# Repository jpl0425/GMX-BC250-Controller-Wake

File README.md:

# GMX BC-250 Controller Wake (Rev 1.2)

Grumblymanx Mods — turns an AMD BC-250 (running Bazzite) **on** when you switch on an
**Xbox Series X|S controller**, using a Raspberry Pi **Pico W** or **Pico 2 W**.

The Pico stays powered from the ATX power supply's +5VSB standby line and listens for the
controller's Bluetooth LE broadcast. When it hears a saved controller it (optionally) switches
the power supply on via PS_ON, "presses" the BC-250 power button with a MOSFET, then waits for
the BC-250's "PC is on" signal (TPMS1 pin 9). The controller still connects to the BC-250 as normal.

> **Status:** firmware compiles cleanly for both boards but has **not yet been tested on real hardware**. The Pico shell has **not been test-printed yet**.

## Revisions
| Folder | What it is |
|---|---|
| `Rev 1.2/` | **Newest.** Install guide Rev 1.2: two completely separate install options (A: power supply always on, B: Pico switches the power supply), one step per page, a realistic picture for every step, page numbers for each option on the first page. Firmware Rev 1 (unchanged). Includes the 3D-printed Pico Shell. |
| `Rev 1.1/` | Previous: guide Rev 1.1 with BC-250 / ATX renders, firmware Rev 1, Pico Shell Rev 1. |

Inside `Rev 1.2/`:
| Folder | Contents |
|---|---|
| `Firmware/` | `GMX-BC250-Wake_Rev1_PicoW.uf2` (Pico W, RP2040) and `GMX-BC250-Wake_Rev1_Pico2W.uf2` (Pico 2 W, RP2350) |
| `Docs/` | Install guide (PDF) — start here, choose Option A or B on page 1. Also the Pico Shell print/assembly guide |
| `Renders/` | Every step picture (`S_A..` Option A, `S_B..` Option B, others shared) + BC-250 renders R1–R4 + Pico Shell pictures |
| `STL/`, `STEP/` | Pico Shell enclosure print and CAD files |
| `Source/` | Firmware source (Pico SDK 2.2.0 + BTstack), Pico Shell source, and the scripts that make the pictures and the guide |

## Optional PCB — GMX BC-250 Wake Board (+ 3D-printed shell)
A small board that replaces the perfboard build. The Pico W / Pico 2 W plugs into two 1x20 sockets;
BSS138LT1G MOSFETs (Q1, Q2), 1N5819WS diode (D1), resistors and the SW1 button are on the board;
outside wires solder to six labelled pads (J3–J8). Works for Option A and Option B (Option A: Q2, R2 and J5 not needed). Same firmware.

| Folder | What it is |
|---|---|
| `PCB/GMX-BC250-Wake-Board_Rev1.1/` | **Newest.** 70.5 × 43 mm board with 4 × M3 mounting holes, plus the 3D-printed **Wake Board Shell Rev 1** (Base, Button, 4 lids: GMX-Mods, Bazzite, BC-250, Blank) and its print/assembly guide |
| `PCB/GMX-BC250-Wake-Board_Rev1.0/` | Previous: 58 × 43 mm board, no mounting holes (does not fit the shell) |

Inside each PCB folder: `Gerbers/`, `BOM/`, `JLC_BOM/`, `CPL/`, `ibom/`, `Renders/`, `Docs/` (wiring diagrams, reports, shell guide), `Firmware/`, `Source/`; Rev 1.1 also has `STL/` and `STEP/` for the shell.

> The PCB and the shell have **not been ordered, printed or tested yet**.

## Pins (Pico GPIO)
GP2 power-button MOSFET · GP3 PS_ON MOSFET (Option B) · GP4 PC-on sense · GP5 optional button · GP6 optional LED · VSYS ← +5VSB through a Schottky diode

## Credits
Wake method from **dexikdex** (ESP32-BC250-LOP_PSU-PowerON-Xbox) and **GreatApo** (BC250_ESP32_ATX_PSU).
BC-250 details from **tfabris/BC-250** and the **elektricm amd-bc250-docs**. New Pico firmware written for this project.

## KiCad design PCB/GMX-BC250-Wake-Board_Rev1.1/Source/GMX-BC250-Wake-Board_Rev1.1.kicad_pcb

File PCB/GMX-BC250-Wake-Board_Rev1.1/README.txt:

GMX BC-250 Wake Board - Rev 1.1  (GMX Mods)
============================================

A small PCB that replaces the perfboard build of the GMX BC-250 Controller Wake
project. A Raspberry Pi Pico W or Pico 2 W plugs into two 1x20 sockets on the board.
Same firmware as the Controller Wake project (Firmware folder) - no changes.

Board: 70.5 x 43 mm, 2 layers, ground pour both sides, 4 x M3 mounting holes (H1-H4).
Rev 1.1 change: board widened and 4 M3 holes added for the 3D-printed shell. Circuit unchanged.
Outside wires solder to 6 labelled wire pads along the top edge (J3-J8).
Works for Option A (power supply always on) and Option B (Pico switches the supply).
For Option A, Q2 and R2 can be left off and J5 stays empty.

FOLDERS
  Gerbers   Gerber + drill zip - upload this to JLCPCB to order the bare board
  BOM       full parts list with LCSC numbers
  JLC_BOM   BOM in JLCPCB's format (SMD parts only) - only if JLCPCB fits the parts
  CPL       placement file for JLCPCB (SMD parts only) - only if JLCPCB fits the parts
  ibom      interactive BOM - open in a web browser while hand-soldering
  Renders   pictures of the board (bare, with parts, with the Pico) and of the shell
  STL       3D-printed shell, print-ready: Base, Button and 4 lids (print one lid)
  STEP      3D-printed shell CAD files
  Docs      wiring diagrams (Option A, Option B), shell print/assembly guide (PDF),
            DRC report, cross-check report, shell fit-check report
  Firmware  .uf2 files: PicoW for a Pico W, Pico2W for a Pico 2 W
  Source    KiCad 7 board, footprint libraries, build scripts; Source/shell = shell CadQuery source

PARTS
  Q1, Q2  BSS138LT1G      SOT-23   LCSC C82045
  R1, R2  10k 0603        YAGEO RC0603FR-0710KL   LCSC C98220
  R3      1k 0603         YAGEO RC0603FR-071KL    LCSC C22548
  D1      1N5819WS        SOD-323  LCSC C191023
  SW1     TS-1187A-B-A-B  5.1 x 5.1 mm SMD button  LCSC C318884
  J1, J2  female socket 1x20, 2.54 mm  ZHOURI PM2.54-1*20  LCSC C5224030
          (alternative: BOOMELE 2.54-1*20P, LCSC C50984)
  Q2 and R2: Option B only.

ORIENTATION
  D1: the band on the part goes toward the right edge of the board (silkscreen bar).
  Q1, Q2: the dot on the silkscreen marks the gate (pin 1).
  Pico: parts side up, USB end at the right edge ("Pin 1" is printed on the board).

SHELL
  Print Base + Button + one lid. 4 x M3 x 6 mm pan-head screws hold the board.
  Start with Docs/GMX-BC250-Wake-Board-Shell_Rev1_Guide.pdf.

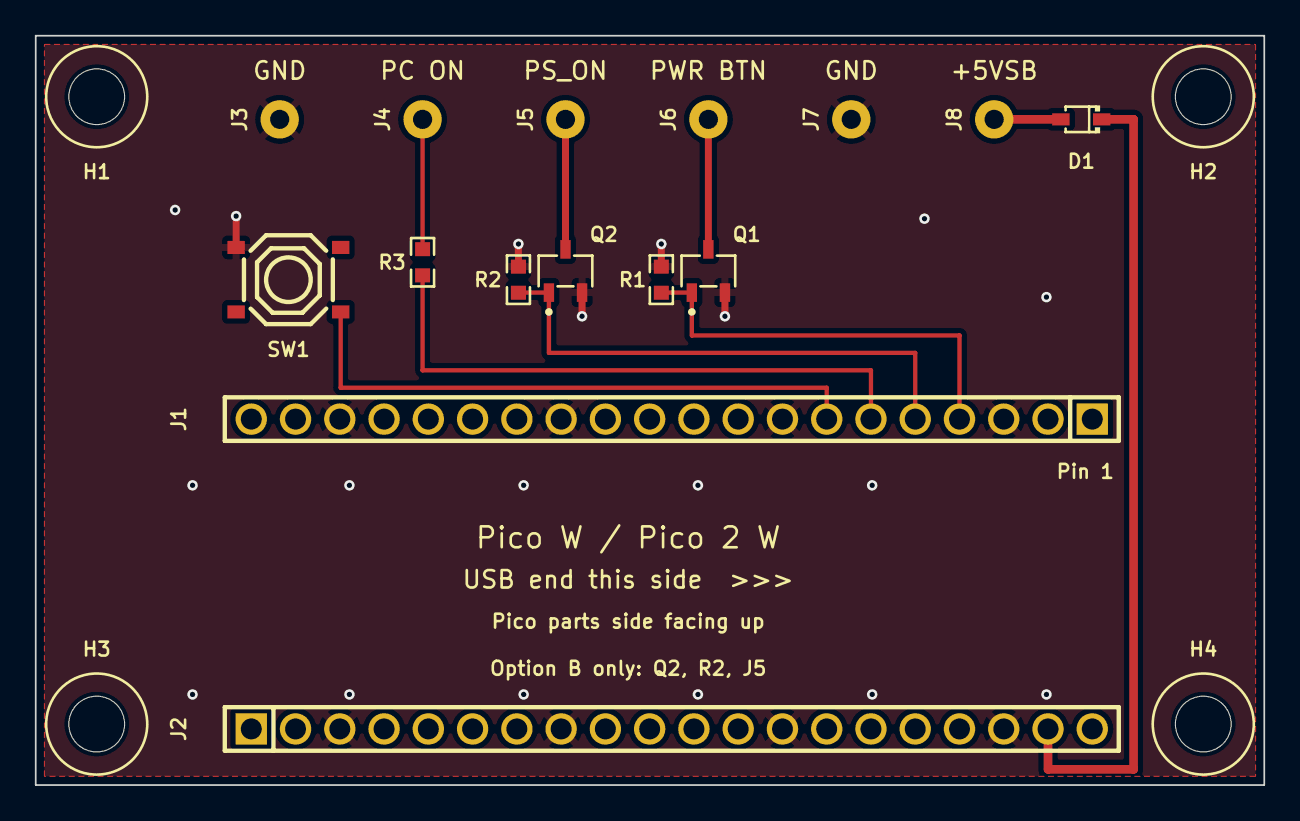
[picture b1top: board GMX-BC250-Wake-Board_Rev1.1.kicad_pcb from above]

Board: 2 copper layers, 70.5 x 43.0 mm, 20 parts (1 on the bottom side), 10 nets.

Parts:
D1: 1N5819WS; SOD-323_L1.8-W1.3-LS2.5-RD
H1, H2, H3, H4: M3 mounting hole; MountingHole_3.2mm_M3
J1: Socket 1x20 (Pico pins 1-20); HDR-TH_20P-P2.54-V-F
J2: Socket 1x20 (Pico pins 21-40); HDR-TH_20P-P2.54-V-F
J3, J7: Wire pad GND; WirePad_D2.2_Drill1.1
J4: Wire pad PC ON; WirePad_D2.2_Drill1.1
J5: Wire pad PS_ON; WirePad_D2.2_Drill1.1
J6: Wire pad PWR BTN; WirePad_D2.2_Drill1.1
J8: Wire pad +5VSB; WirePad_D2.2_Drill1.1
LOGO1: GMX_Mods_Logo_Silk_22mm
Q1, Q2: BSS138LT1G; SOT-23-3_L2.9-W1.6-P1.90-LS2.8-BR
R1, R2: 10k; R0603
R3: 1k; R0603
SW1: TS-1187A-B-A-B; SW-SMD_4P-L5.1-W5.1-P3.70-LS6.5-TL_H1.5

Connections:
+5VSB: D1.2, J8.1
GND: J1.3, J1.8, J1.13, J1.18, J2.3, J2.8, J2.13, J2.18, J3.1, J7.1, Q1.2, Q2.2, R1.2, R2.2, SW1.1
GP2_PWRBTN: J1.4, Q1.1, R1.1
GP3_PSON: J1.5, Q2.1, R2.1
GP4_SENSE: J1.6, R3.1
GP5_SW: J1.7, SW1.4
PC_ON: J4.1, R3.2
PS_ON: J5.1, Q2.3
PWR_BTN: J6.1, Q1.3
VSYS: D1.1, J2.19

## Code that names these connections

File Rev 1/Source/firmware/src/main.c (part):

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#define FW_VERSION  "Rev1 (1.0.0)"

/* ---------------- pins ---------------- */
#define PIN_PWR_BTN   2
#define PIN_PS_ON     3
#define PIN_PC_SENSE  4
#define PIN_BUTTON    5
#define PIN_EXT_LED   6

/* ---------------- timings (ms) ---------------- */
#define PSU_SETTLE_MS            1000u   /* PS_ON on -> wait before button  */
#define BUTTON_PRESS_MS           500u   /* power-button pulse length       */
#define WAIT_FOR_PC_ON_MS       20000u   /* give up if PC not on by then    */
#define WAKE_COOLDOWN_MS        15000u   /* ignore controller after a wake  */
#define SHUTDOWN_IGNORE_MS      60000u   /* ignore controller after PC off  */
#define PSU_OFF_DELAY_MS        10000u   /* PC off this long -> PS_ON off   */
#define SENSE_DEBOUNCE_MS         100u
#define BOOT_IGNORE_MS           3000u   /* ignore controller right after boot */
#define LEARN_IGNORE_MS         30000u   /* ignore controllers after learn mode ends */
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static void set_ps_on(bool on) {
    if (on != ps_on_active) printf("[PSU] PS_ON %s\n", on ? "ON (supply on)" : "OFF (supply may switch off)");
    ps_on_active = on;
    gpio_put(PIN_PS_ON, on);
}

static void set_pwr_btn(bool pressed) { gpio_put(PIN_PWR_BTN, pressed); }

static void set_led(bool on) {
    static int last = -1;
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/* ======================================================================= */
int main(void) {
    /* Outputs first, driven LOW = MOSFETs off (nothing pressed, PS_ON untouched) */
    gpio_init(PIN_PWR_BTN); gpio_set_dir(PIN_PWR_BTN, GPIO_OUT); gpio_put(PIN_PWR_BTN, 0);
    gpio_init(PIN_PS_ON);   gpio_set_dir(PIN_PS_ON, GPIO_OUT);   gpio_put(PIN_PS_ON, 0);
    gpio_init(PIN_EXT_LED); gpio_set_dir(PIN_EXT_LED, GPIO_OUT); gpio_put(PIN_EXT_LED, 0);
    gpio_init(PIN_PC_SENSE); gpio_set_dir(PIN_PC_SENSE, GPIO_IN); gpio_pull_down(PIN_PC_SENSE);
    gpio_init(PIN_BUTTON);   gpio_set_dir(PIN_BUTTON, GPIO_IN);   gpio_pull_up(PIN_BUTTON);
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
    /* If the PC is already running when the Pico starts, keep the supply on */
    sleep_ms(20);
    pc_on = gpio_get(PIN_PC_SENSE);
    sense_raw_last = pc_on;
    if (pc_on) set_ps_on(true);

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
